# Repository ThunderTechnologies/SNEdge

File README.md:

# SNEdge - An Opensource SNES Edge Sharpener
**This has only been tested on a few SNES revisions | Proceed with caution**

SNEdge V2 is to a state where it can be considered stable. As SNES revisions are tested, instructions will be added to the wiki.
For now, only the full bypass is supported. The sidecar install will get a dedicated design at some point.

The SNEdge corrects much of the smearing that's present on the 2 chip SNES. It taps the console's RGB, cleanly buffers it, and applies a tuned amount of sharpening to bring back the crisp edges the stock 2 chip output loses.

This is the latest revision of the SNEdge. Over the original it refines the input biasing, properly impedance-matches the outputs to the 75Ω video standard, and re-tunes the sharpening — see [How It Works](#how-it-works) for the details. It still uses 0805 components, so it's relatively approachable to solder by hand.

The SNEdge pairs with the **Multiout QSB**, which makes for a clean install right at the multiout. There are two ways to connect the SNEdge to the QSB:

- **U.FL Coax (recommended)** — connect the two boards with U.FL-terminated 1.13mm coax (the same cable sold as WiFi antenna pigtails). This is the preferred method for new installs: it's a higher-quality, shielded connection, the U.FL connectors let you position and route the cable freely, and the cable is cheaper and easier to source than FFC. Around 10cm length works well.
- **FFC cable** — a single ribbon cable between the two boards. Still supported, but coax is the better choice going forward.

> Where to get the boards:<br />
[SNEdge V2 Gerbers](https://github.com/ThunderTechnologies/SNEdge/tree/SNEdge_V2/SNEdge%20PCB/Manufacturing)<br />
[FFC QSB Gerbers](https://github.com/ThunderTechnologies/SNEdge/tree/SNEdge_V2/Multi%20AV%20QSB/FFC%20QSB/Manufacturing)<br />
[Coax QSB Gerbers](https://github.com/ThunderTechnologies/SNEdge/tree/SNEdge_V2/Multi%20AV%20QSB/U.FL%20QSB/Manufacturing)<br />
Note:  The coax is standard U.FL 1.13mm WiFi antenna pigtail cable (roughly 10cm), widely available online.<br />

The SNEdge

The Multiout U.FL QSB

The Multiout FFC QSB

(I'll be adding screenshots of the video output soon)

## How It Works

The SNEdge taps the RGB video signal at the PPU2 output (the Q3/Q5/Q7 points) and runs each channel through a THS7376 video amplifier. The 2 chip SNES PPU has slow color transitions that show up on screen as smearing; cleanly buffering the signal and applying a small amount of high-frequency peaking sharpens those transitions without changing the rest of the picture.

A few design choices worth knowing about:

- **Ground reference and input attenuation.** Each RGB input has a 7.5kΩ pull-down resistor. It does two jobs. First, it gives the amplifier input a proper, defined ground/DC reference so the signal sits where it should. Second, it attenuates the input down to around 2.20Vptp, which keeps the signal within the THS7376's 2.35Vptp linear input voltage spec and so avoids clipping the amplifier's input. For context, the SNES's original RGB amp has an input impedance of about 12kΩ.
- **Sharpening.** A small feedback capacitor on each channel provides the edge sharpening. It's tuned for the most sharpening you can get before overshoot starts to become visible.
- **75Ω output.** Each output uses a 240Ω / 110Ω network. The thevenin equivalent is about 75Ω, which is the standard video source impedance, so the SNEdge drives a cable correctly.
- **Optional noise caps.** Adding a 10uF cap to each of C90-C94 on the SNES motherboard helps suppress video noise. These are optional — you can leave them out and only add them if you notice any noticeable noise in the output.

## Installation
I don't have specific, picture instructions on how to install the SNEdge yet (These will be slowly added to the wiki).

However, looking at the [SNES schematic (PDF)](https://wiki.superfamicom.org/uploads/snes_schematic_color.pdf) from [wiki.superfamicom.org](wiki.superfamicom.org) will be critical for understanding how to install this.

This revision installs using the **RGB Bypass** method, which gives the best sharpness. The older **Sidecar** method (which didn't require desoldering any components) is no longer supported on this revision — see [A Note on the Sidecar Install](#a-note-on-the-sidecar-install) below if that's what you're after.

Optionally, you can solder an additional 10uF capacitor onto C90, C91, C92, C93, and C94 on the SNES motherboard (for PAL systems, it's C91, C92, C93, C94, and C95). These help reduce video noise. They aren't required, but if you notice any noticeable noise in the output, adding them should clean it up.

Below is an SOT-23 pinout I will be referencing later.

### A Note on the Sidecar Install
The Sidecar method is **not supported on this revision.** If you want a sidecar-style install, the original SNEdge can still be used for that. A dedicated sidecar revision may be released later by ThunderTechnologies.

This revision has not been tested in a sidecar configuration. It may work fine, but it's untested, so it isn't documented as a supported install here. For this revision, use the Full RGB Bypass install below.

### Full RGB Bypass Install
(Please note that PAL system installation is a bit different, I have info on this, and will be adding it eventually.)

Mount the SNEdge, keeping one priority above everything else: **keep the input wires as short as possible.**

The R, G, and B input wires are very sensitive to parasitic capacitance, so position the SNEdge so those wires reach their mainboard points (Q3, Q5, Q7) over the shortest distance you can manage. Keeping the input wires as close to the mainboard points as possible is the single most important part of placement. It's also preferred to keep the three input wires at **similar lengths** to each other.

Orientation depends on how you're connecting to the QSB:

- **Coax (recommended):** the U.FL coax gives you a lot of freedom. Orient and place the SNEdge however best keeps the input wires short, and route the coax wherever is convenient.
- **FFC:** point the FFC connector toward the multiout of the SNES.

Remove Q3, Q5, and Q7. If you only care about RGB working, remove R8, R9, R13, R14, R18, and R19. If you also care about Composite video and S-Video, also remove C6, C7, and C8.

Q3 is Red, Q5 is Green, and Q7 is Blue. Looking at the SOT-23 pinout above, pin 3 of each is ground. Pin 1 of each is the R, G, and B signals that will be soldered to the SNEdge.

Solder leads from Q3 to R_IN and GND.

Solder leads from Q5 to G_IN and GND.

Solder leads from Q7 to B_IN and GND.

The SNEdge needs to output video to U7 (S-ENC) on the SNES in order for composite video and S-video.

The SNEdge R_E, G_E, and B_E outputs go to U7's pins 20, 21, 22 respectively. (you can ignore the GND pin next to these if you'd like. If you care, connect it to pin 2 of U7.

Solder the multiout QSB on to the bottom of the SNES where the multiout pins are. If you're looking at the bottom of the SNES board, the "TOP" label on the QSB needs to be facing you. (If you're using FFC, also orient it so the FFC connector points toward the SNEdge; with coax, routing is flexible so this doesn't matter.)

The SNEdge needs 5V. Solder 5V to the + and ground to the -

Connect the SNEdge to the QSB. Coax is the recommended method:

- **Coax (recommended):** connect the SNEdge to the QSB with U.FL-terminated 1.13mm coax (the cable commonly sold as WiFi antenna pigtails). Around 10cm length works well. It's the better-quality connection, easy to route thanks to the U.FL connectors, and cheap to source.
- **FFC cable:** alternatively, connect an FFC cable between the SNEdge and the QSB. The contacts of the FFC face down, with the blue tabs facing up.

Congrats! You have completed the full RGB bypass install. Enjoy some crispy RGB.

### A Note on PAL Systems
**PAL has not been tested yet.** The SNEdge should work on PAL consoles since they share the same PPU, but please treat PAL installs as experimental for now.

The main difference to be aware of is the cap designators: if you add the optional noise-reduction caps, on PAL systems they go on **C91, C92, C93, C94, and C95** instead of C90-C94. PAL boards also differ around the encoder, so the Full RGB Bypass encoder connections (the U7 pin references above) may not match a PAL console one-to-one. Until PAL-specific details are confirmed and documented, treat a PAL install as experimental and proceed carefully. More complete PAL instructions will be added as they're verified.

### Credits

The SNEdge is based on the work of YoshiYukiBlade over on the [shmups.system11.org](https://shmups.system11.org/viewtopic.php?t=70196) forums.<br />
V2 was made possible by the many contributions from [RetroLoom](https://github.com/RetroLoom)

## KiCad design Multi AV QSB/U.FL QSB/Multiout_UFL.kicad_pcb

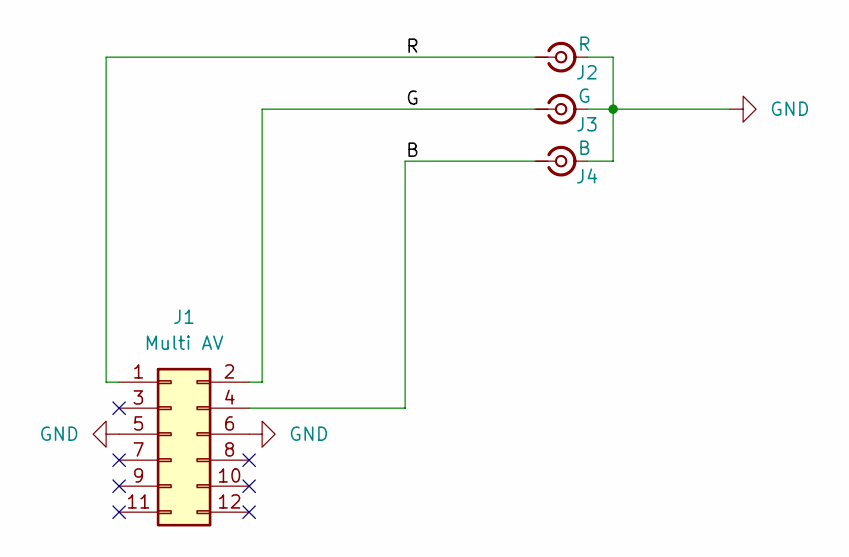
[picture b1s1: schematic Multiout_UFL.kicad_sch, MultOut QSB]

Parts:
J1: Multi AV; Multi_AV_QSB
J2: R; U.FL_Hirose_U.FL-R-SMT-1_Vertical; MFG_PN U.FL-R-SMT-1(10); Digi_PN H11891CT-ND
J3: G; U.FL_Hirose_U.FL-R-SMT-1_Vertical; MFG_PN U.FL-R-SMT-1(10); Digi_PN H11891CT-ND
J4: B; U.FL_Hirose_U.FL-R-SMT-1_Vertical; MFG_PN U.FL-R-SMT-1(10); Digi_PN H11891CT-ND

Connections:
/B: J1.4, J4.1 (In)
/G: J1.2, J3.1 (In)
/R: J1.1, J2.1 (In)
GND: J1.5, J1.6, J2.2 (Ext), J3.2 (Ext), J4.2 (Ext)

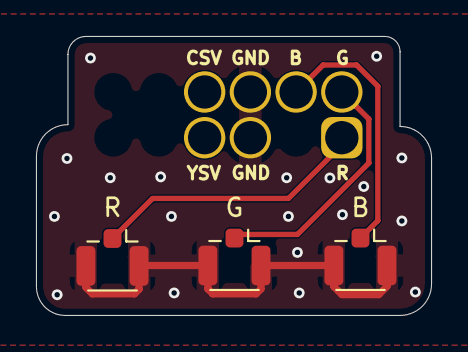
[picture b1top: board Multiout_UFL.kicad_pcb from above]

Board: 2 copper layers, 21.9 x 15.5 mm, 4 parts (0 on the bottom side), 4 nets.

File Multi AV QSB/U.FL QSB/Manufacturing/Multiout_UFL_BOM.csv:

"Reference","Value","Qty","Digi_PN","MFG_PN"
"J2","R","1","H11891CT-ND","U.FL-R-SMT-1(10)"
"J3","G","1","H11891CT-ND","U.FL-R-SMT-1(10)"
"J4","B","1","H11891CT-ND","U.FL-R-SMT-1(10)"

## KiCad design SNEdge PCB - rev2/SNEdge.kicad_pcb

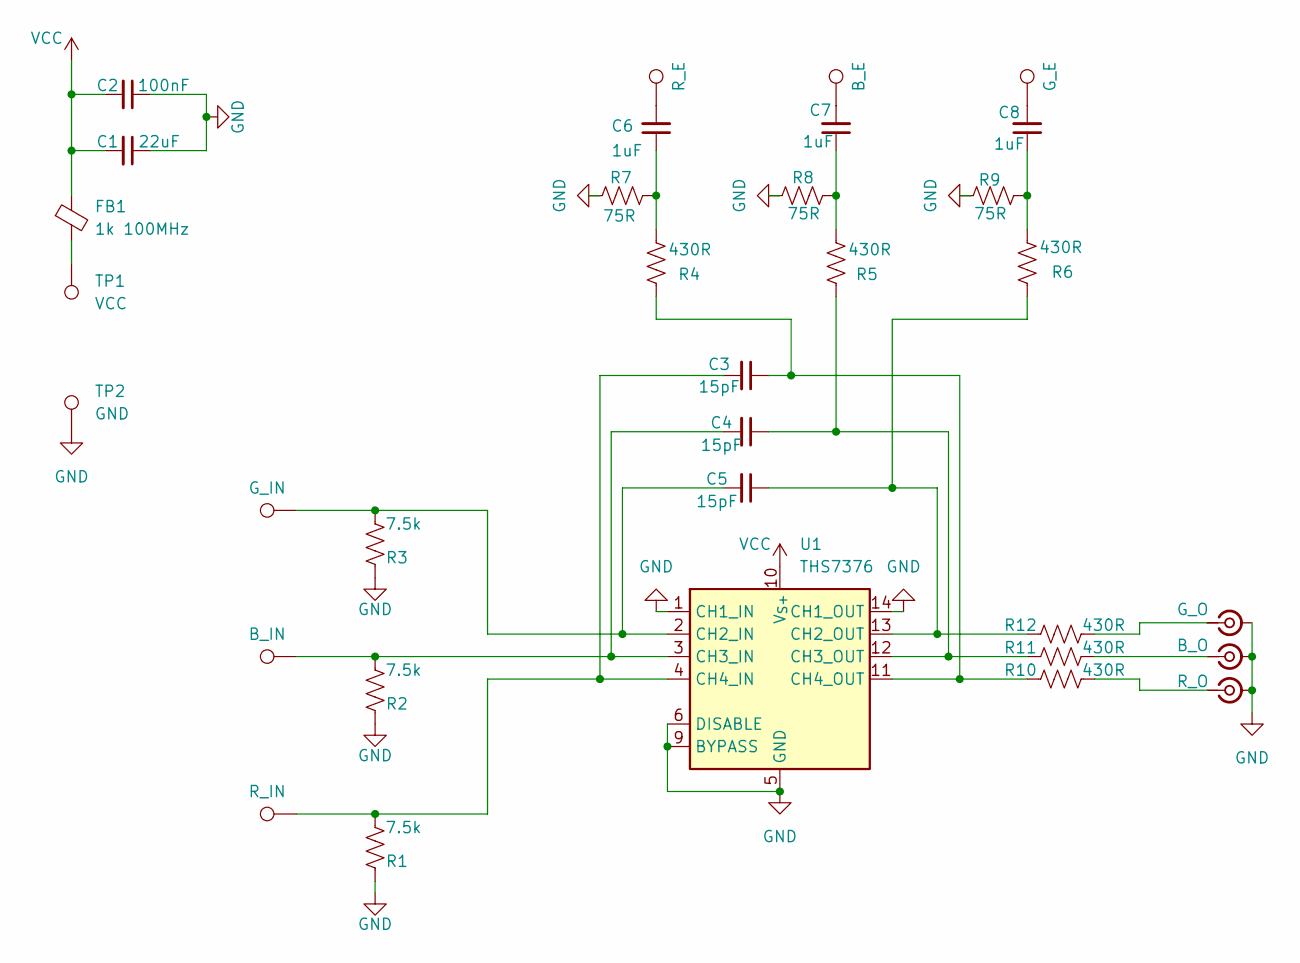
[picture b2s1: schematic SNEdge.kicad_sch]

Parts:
C1: 22uF; C_0805_2012Metric_Pad1.18x1.45mm_HandSolder
C2: 100nF; C_0805_2012Metric_Pad1.18x1.45mm_HandSolder
C3, C4, C5: 15pF; C_0805_2012Metric_Pad1.18x1.45mm_HandSolder
C6, C7, C8: 1uF; C_0805_2012Metric_Pad1.18x1.45mm_HandSolder
FB1: 1k 100MHz; R_0805_2012Metric_Pad1.20x1.40mm_HandSolder
J8: G_O; U.FL_Hirose_U.FL-R-SMT-1_Vertical
J9: B_O; U.FL_Hirose_U.FL-R-SMT-1_Vertical
J10: R_O; U.FL_Hirose_U.FL-R-SMT-1_Vertical
R1, R2, R3: 7.5k; R_0805_2012Metric_Pad1.20x1.40mm_HandSolder
R4, R5, R6, R10, R11, R12: 430R; R_0805_2012Metric_Pad1.20x1.40mm_HandSolder
R7, R8, R9: 75R; R_0805_2012Metric_Pad1.20x1.40mm_HandSolder
TP1: VCC; TestPoint_Pad_1.5x1.5mm; MFG_PN N/A; Digi_PN N/A
TP2: GND; TestPoint_Pad_1.5x1.5mm; MFG_PN N/A; Digi_PN N/A
TP3: G_IN; TestPoint_Pad_1.5x1.5mm; MFG_PN N/A; Digi_PN N/A
TP4: B_IN; TestPoint_Pad_1.5x1.5mm; MFG_PN N/A; Digi_PN N/A
TP5: R_IN; TestPoint_Pad_1.5x1.5mm; MFG_PN N/A; Digi_PN N/A
TP6: R_E; TestPoint_Pad_1.5x1.5mm; MFG_PN N/A; Digi_PN N/A
TP7: B_E; TestPoint_Pad_1.5x1.5mm; MFG_PN N/A; Digi_PN N/A
TP8: G_E; TestPoint_Pad_1.5x1.5mm; MFG_PN N/A; Digi_PN N/A
U1: THS7376; TSSOP-14_4.4x5mm_P0.65mm

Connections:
GND: C1.1, C2.1, J8.2 (Ext), J9.2 (Ext), J10.2 (Ext), R1.1, R2.1, R3.1, R7.2, R8.2, R9.2, TP2.1, U1.1 (CH1_IN), U1.5 (GND), U1.6 (DISABLE), U1.9 (BYPASS), U1.14 (CH1_OUT)
unnamed: C6.1, R4.2, R7.1
unnamed: C6.2, TP6.1
unnamed: C7.1, R5.2, R8.1
unnamed: C7.2, TP7.1
unnamed: C8.1, R6.2, R9.1
unnamed: C8.2, TP8.1
unnamed: FB1.2, TP1.1
unnamed: J8.1 (In), R12.1
unnamed: J9.1 (In), R11.1
unnamed: J10.1 (In), R10.1
unnamed: C5.2, R3.2, TP3.1, U1.2 (CH2_IN)
unnamed: C5.1, R6.1, R12.2, U1.13 (CH2_OUT)
unnamed: C4.2, R2.2, TP4.1, U1.3 (CH3_IN)
unnamed: C4.1, R5.1, R11.2, U1.12 (CH3_OUT)
unnamed: C3.2, R1.2, TP5.1, U1.4 (CH4_IN)
unnamed: C3.1, R4.1, R10.2, U1.11 (CH4_OUT)
VCC: C1.2, C2.2, FB1.1, U1.10 (V_{S+})

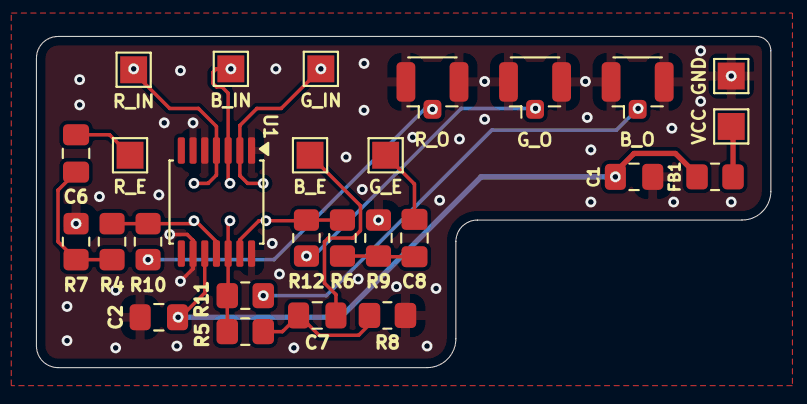
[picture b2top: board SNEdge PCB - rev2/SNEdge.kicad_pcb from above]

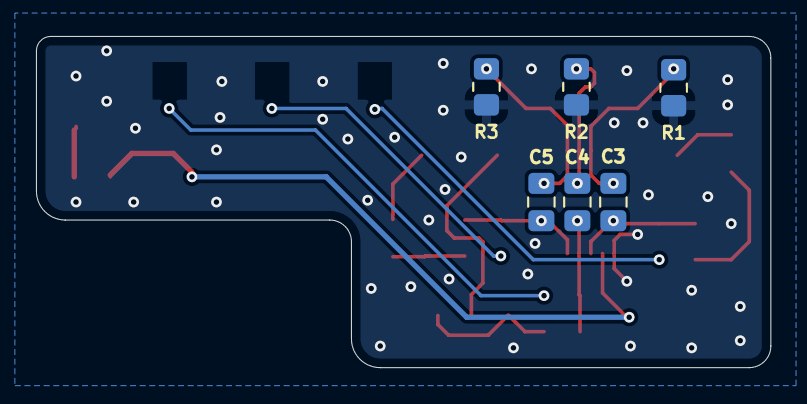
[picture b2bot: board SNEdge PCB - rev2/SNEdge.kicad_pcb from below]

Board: 2 copper layers, 40.8 x 18.4 mm, 33 parts (6 on the bottom side), 18 nets.

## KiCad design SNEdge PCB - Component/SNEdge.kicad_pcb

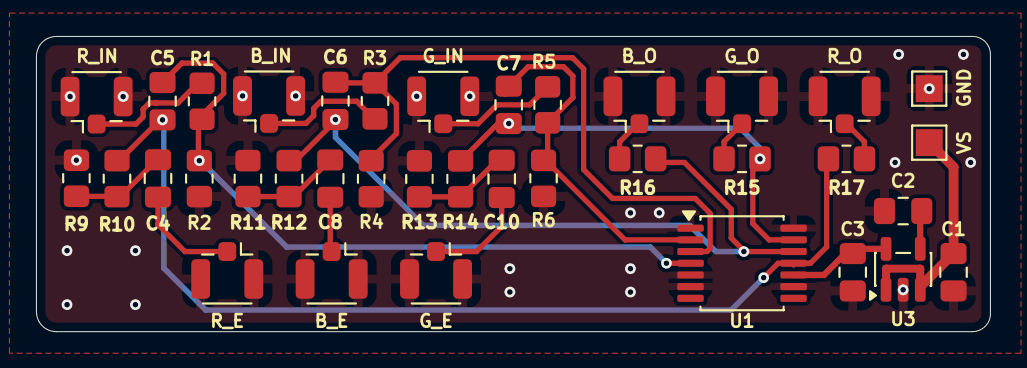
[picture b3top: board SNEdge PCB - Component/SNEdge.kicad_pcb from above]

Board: 2 copper layers, 53.0 x 16.4 mm, 37 parts (0 on the bottom side), 22 nets.

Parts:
C1: 1uF; C_0805_2012Metric_Pad1.18x1.45mm_HandSolder
C2: 470pF; C_0805_2012Metric_Pad1.18x1.45mm_HandSolder
C3: 10uF; C_0805_2012Metric_Pad1.18x1.45mm_HandSolder
C4, C8, C10: 100nF; C_0805_2012Metric_Pad1.18x1.45mm_HandSolder
C5, C6, C7: 27pF; C_0805_2012Metric_Pad1.18x1.45mm_HandSolder
J2: R_E; U.FL_Hirose_U.FL-R-SMT-1_Vertical
J3: B_E; U.FL_Hirose_U.FL-R-SMT-1_Vertical
J4: G_E; U.FL_Hirose_U.FL-R-SMT-1_Vertical
J5: G_IN; U.FL_Hirose_U.FL-R-SMT-1_Vertical
J6: B_IN; U.FL_Hirose_U.FL-R-SMT-1_Vertical
J7: R_IN; U.FL_Hirose_U.FL-R-SMT-1_Vertical
J8: G_O; U.FL_Hirose_U.FL-R-SMT-1_Vertical
J9: B_O; U.FL_Hirose_U.FL-R-SMT-1_Vertical
J10: R_O; U.FL_Hirose_U.FL-R-SMT-1_Vertical
R1, R3, R5: 1.5k; R_0805_2012Metric_Pad1.20x1.40mm_HandSolder
R2, R4, R6: 10k; R_0805_2012Metric_Pad1.20x1.40mm_HandSolder
R9, R11, R13: 220R; R_0805_2012Metric_Pad1.20x1.40mm_HandSolder
R10, R12, R14: 1k; R_0805_2012Metric_Pad1.20x1.40mm_HandSolder
R15, R16, R17: 360R; R_0805_2012Metric_Pad1.20x1.40mm_HandSolder
TP1: VS; TestPoint_Pad_1.5x1.5mm
TP2: GND; TestPoint_Pad_1.5x1.5mm
U1: THS7374; TSSOP-14_4.4x5mm_P0.65mm
U3: MIC5205-5.0YM5; SOT-23-5

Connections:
GND: C1.1, C2.1, C3.1, J2.2 (Ext), J3.2 (Ext), J4.2 (Ext), J5.2 (Ext), J6.2 (Ext), J7.2 (Ext), J8.2 (Ext), J9.2 (Ext), J10.2 (Ext), R2.2, R4.2, R6.2, R9.2, R11.2, R13.2, TP2.1, U1.1 (CH1_IN), U1.5 (GND), U1.6 (DISABLE), U1.9 (BYPASS), U1.14 (CH1_OUT), U3.2 (GND)
unnamed: C4.1, R9.1, R10.2
unnamed: C8.1, R11.1, R12.2
unnamed: C10.1, R13.1, R14.2
unnamed: C4.2, J2.1 (In)
unnamed: C8.2, J3.1 (In)
unnamed: C10.2, J4.1 (In)
unnamed: J5.1 (In), R5.1
unnamed: J6.1 (In), R3.1
unnamed: J7.1 (In), R1.1
unnamed: J8.1 (In), R15.1
unnamed: J9.1 (In), R16.1
unnamed: J10.1 (In), R17.1
unnamed: C7.2, R5.2, R6.1, U1.2 (CH2_IN)
unnamed: C7.1, R14.1, R15.2, U1.13 (CH2_OUT)
unnamed: C6.2, R3.2, R4.1, U1.3 (CH3_IN)
unnamed: C6.1, R12.1, R16.2, U1.12 (CH3_OUT)
unnamed: C5.2, R1.2, R2.1, U1.4 (CH4_IN)
unnamed: C5.1, R10.1, R17.2, U1.11 (CH4_OUT)
unnamed: C2.2, U3.4 (BP)
VCC: C3.2, U1.10 (V_{S+}), U3.5 (OUT)
VS: C1.2, TP1.1, U3.1 (IN), U3.3 (EN)

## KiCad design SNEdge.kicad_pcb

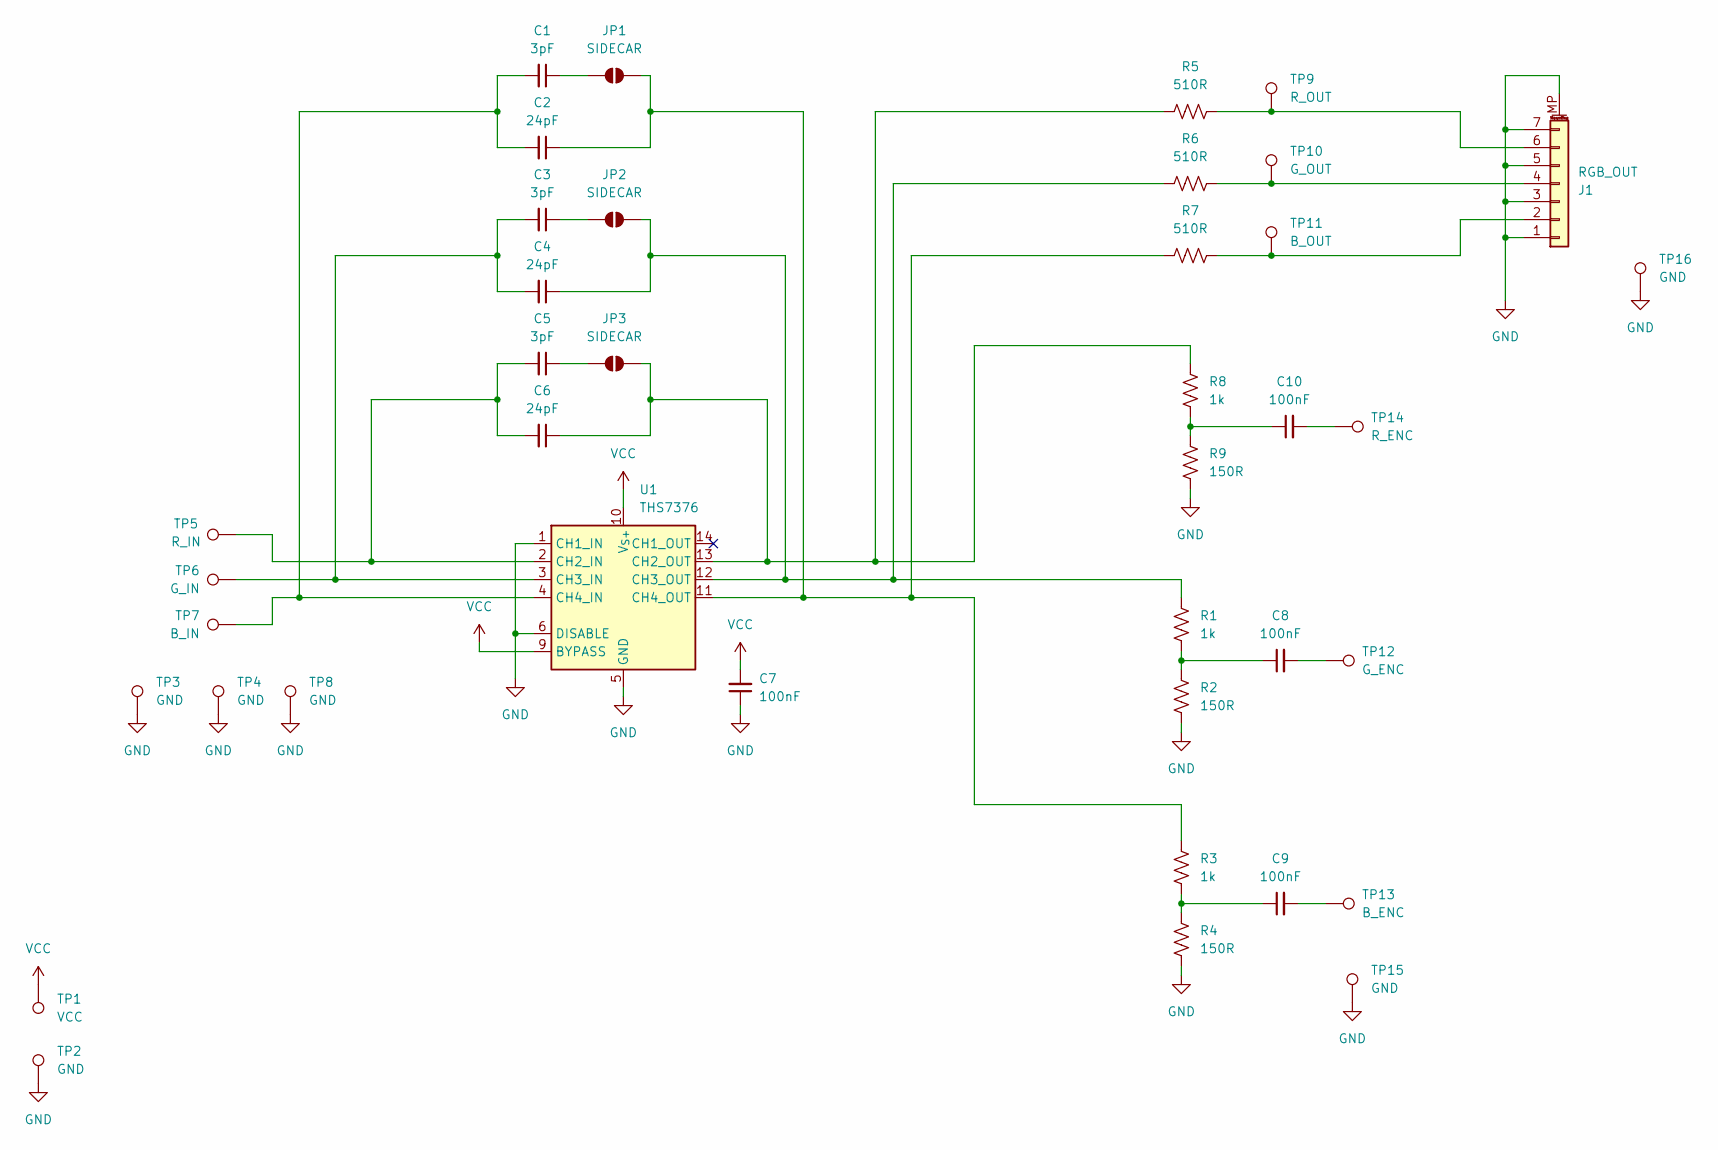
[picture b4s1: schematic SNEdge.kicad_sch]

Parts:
C1, C3, C5: 3pF; C_0805_2012Metric; MFG_PN CC0805CRNPO9BN3R0; Digi_PN 311-1092-1-ND
C2, C4, C6: 24pF; C_0805_2012Metric; MFG_PN 08051A240FAT2A; Digi_PN 478-10387-1-ND
C7, C8, C9, C10: 100nF; C_0805_2012Metric; MFG_PN CL21B104KBCNFNC; Digi_PN 1276-2444-1-ND
J1: RGB_OUT; CON_527460771_MOL; MFG_PN 0527460771; Digi_PN WM8933CT-ND
JP1, JP2, JP3: SIDECAR; SolderJumper-2_P1.3mm_Open_RoundedPad1.0x1.5mm; MFG_PN N/A; Digi_PN N/A
R1, R3, R8: 1k; R_0805_2012Metric; MFG_PN RMCF0805FT1K00; Digi_PN RMCF0805FT1K00CT-ND
R2, R4, R9: 150R; R_0805_2012Metric; MFG_PN RMCF0805FT150R; Digi_PN RMCF0805FT150RCT-ND
R5, R6, R7: 510R; R_0805_2012Metric; MFG_PN RMCF0805FT510R; Digi_PN RMCF0805FT510RCT-ND
TP1: VCC; TestPoint_Pad_2.0x2.0mm; MFG_PN N/A; Digi_PN N/A
TP2, TP3, TP4, TP8, TP15: GND; TestPoint_Pad_2.0x2.0mm; MFG_PN N/A; Digi_PN N/A
TP5: R_IN; TestPoint_Pad_2.0x2.0mm; MFG_PN N/A; Digi_PN N/A
TP6: G_IN; TestPoint_Pad_2.0x2.0mm; MFG_PN N/A; Digi_PN N/A
TP7: B_IN; TestPoint_Pad_2.0x2.0mm; MFG_PN N/A; Digi_PN N/A
TP9: R_OUT; TestPoint_Pad_1.0x1.0mm; MFG_PN N/A; Digi_PN N/A
TP10: G_OUT; TestPoint_Pad_1.0x1.0mm; MFG_PN N/A; Digi_PN N/A
TP11: B_OUT; TestPoint_Pad_1.0x1.0mm; MFG_PN N/A; Digi_PN N/A
TP12: G_ENC; TestPoint_Pad_2.0x2.0mm; MFG_PN N/A; Digi_PN N/A
TP13: B_ENC; TestPoint_Pad_2.0x2.0mm; MFG_PN N/A; Digi_PN N/A
TP14: R_ENC; TestPoint_Pad_2.0x2.0mm; MFG_PN N/A; Digi_PN N/A
TP16: GND; TestPoint_Pad_1.0x1.0mm; MFG_PN N/A; Digi_PN N/A
U1: THS7376; TSSOP-14_4.4x5mm_P0.65mm; MFG_PN THS7376IPWR; Digi_PN 296-40584-1-ND

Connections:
GND: C7.1, J1.1, J1.3, J1.5, J1.7, J1.MP (MountPin), R2.2, R4.2, R9.2, TP2.1, TP3.1, TP4.1, TP8.1, TP15.1, TP16.1, U1.1 (CH1_IN), U1.5 (GND), U1.6 (DISABLE)
unnamed: C8.1, R1.2, R2.1
unnamed: C8.2, TP12.1
unnamed: C9.1, R3.2, R4.1
unnamed: C9.2, TP13.1
unnamed: C10.1, R8.2, R9.1
unnamed: C10.2, TP14.1
unnamed: J1.2, R7.1, TP11.1
unnamed: J1.4, R6.1, TP10.1
unnamed: J1.6, R5.1, TP9.1
unnamed: C1.1, JP1.1 (A)
unnamed: C2.1, JP1.2 (B), R3.1, R7.2, U1.11 (CH4_OUT)
unnamed: C3.1, JP2.1 (A)
unnamed: C4.1, JP2.2 (B), R1.1, R6.2, U1.12 (CH3_OUT)
unnamed: C5.1, JP3.1 (A)
unnamed: C6.1, JP3.2 (B), R5.2, R8.1, U1.13 (CH2_OUT)
unnamed: C5.2, C6.2, TP5.1, U1.2 (CH2_IN)
unnamed: C3.2, C4.2, TP6.1, U1.3 (CH3_IN)
unnamed: C1.2, C2.2, TP7.1, U1.4 (CH4_IN)
VCC: C7.2, TP1.1, U1.9 (BYPASS), U1.10 (V_{S+})

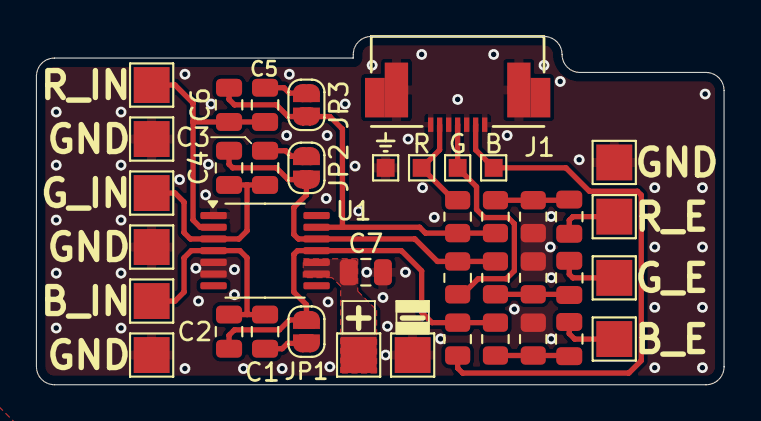
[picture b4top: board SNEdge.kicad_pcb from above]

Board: 2 copper layers, 38.2 x 19.3 mm, 40 parts (0 on the bottom side), 20 nets.

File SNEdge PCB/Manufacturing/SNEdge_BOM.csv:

Item,Qty,Reference(s),Value,Digi_PN,MFG_PN,Type
1,3,"C1, C3, C5",3pF,311-1092-1-ND,CC0805CRNPO9BN3R0,SMD
2,3,"C2, C4, C6",24pF,478-10387-1-ND,08051A240FAT2A,SMD
3,4,"C7, C8, C9, C10",100nF,1276-2444-1-ND,CL21B104KBCNFNC,SMD
4,1,J1,RGB_OUT,WM8933CT-ND,527460771,SMD
5,3,"R1, R3, R8",1k,RMCF0805FT1K00CT-ND,RMCF0805FT1K00,SMD
6,3,"R2, R4, R9",150R,RMCF0805FT150RCT-ND,RMCF0805FT150R,SMD
7,3,"R5, R6, R7",510R,RMCF0805FT510RCT-ND,RMCF0805FT510R,SMD
8,1,U1,THS7376,296-40584-1-ND,THS7376IPWR,SMD
9,1,W1,FFC Cable,WM16420-ND,0150200751,Cable

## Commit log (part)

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2024-08-18 Create LICENSE
2024-08-19 Initial Design
2024-08-19 Rearrange folders
2024-08-19 Created MultiOut QSB
2024-08-19 Added BOM
2024-08-19 Added Schematics
2024-08-31 Prepping for release
2024-10-05 getting ready for alpha release
2024-10-05 removed libre office lock files
2024-10-30 Update README.md
    Started on basic install instructions
2024-11-26 Added SOT-23
2024-11-26 Update README.md
    added sidecar install
2024-11-26 Update README.md
    Added RGB bypass instructions
2024-12-25 Update README.md
    Added credits that I forgot...
2025-01-14 Update SNEdge_BOM.csv
    Added FFC cable PN
2025-01-14 Update SNEdge_BOM.csv
    Forgot a field
2025-03-15 Update README.md
    fixed typo on C92 and added a bit of info on PAL systems
2025-09-06 AC coupled input, SD filter enabled
2025-09-08 SNEdge 2 with component switch
2025-11-10 Cleaned up component side
2025-11-11 Added voltage dividers on RGB input
2025-12-10 Remove component inputs and switch, refine SNEdge
2025-12-10 Change directory name to indicate SNEdge Revision 2
2025-12-11 Reverse RGB output to match QSB
2025-12-11 Add more ground plane stitching
2025-12-12 Multi AV QSB - Coax and Coupling Capacitors
2026-01-07 v2.1 remove voltage divider and voltage regulator, input pull down and power filtering
2026-01-10 Refactor for purity
2026-01-10 Add encoder coupling capacitors back
2026-01-10 Add ground stitching
2026-01-10 Switch position of ferrite bead and bulk capacitor
2026-01-10 Fix input trace length
2026-01-10 Small update to PCB
2026-01-10 QSB - remove AC coupling and add GND lift jumper
2026-01-10 Small SNEdge update for THS VCC decoupling cap
2026-02-12 Update references and a bit of clean up
2026-03-06 V2 based on RetroLoom's Rev2
2026-04-30 Update coax QSB for new RGB order layout
2026-05-04 Adjust feedback capacitors to 10pF
2026-06-07 Updating the branch to include all stuff from collab
2026-06-28 added V2 Render
2026-06-28 Remove redundant rev2 and coax folders
2026-06-28 Update README.md for Rev2
2026-06-28 Update README images
2026-06-28 README remove multi ground input source reference
2026-06-28 Reference input attenuation with 7.5k pull down resistors
2026-06-29 added ohm symbols when talking about resistance added reference to thevenin added some context to original input impedance added links to gerbers removed reference to being an alpha release added cre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
2026-06-29 fixing readme formatting because I barely understand markdown
2026-06-29 still trying to understand markdown :P
2026-06-29 accidentally removed a number. Added it back
2026-06-29 added a few more ohm symbols
2026-06-30 Update README.md
    Corrected formatting mistake in credits
